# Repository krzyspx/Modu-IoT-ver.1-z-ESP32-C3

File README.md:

# Modu-IoT-ver.1-z-ESP32-C3
Projekt PCB (Eagle) dla domowej automatyki z procesorem ESP32 C3

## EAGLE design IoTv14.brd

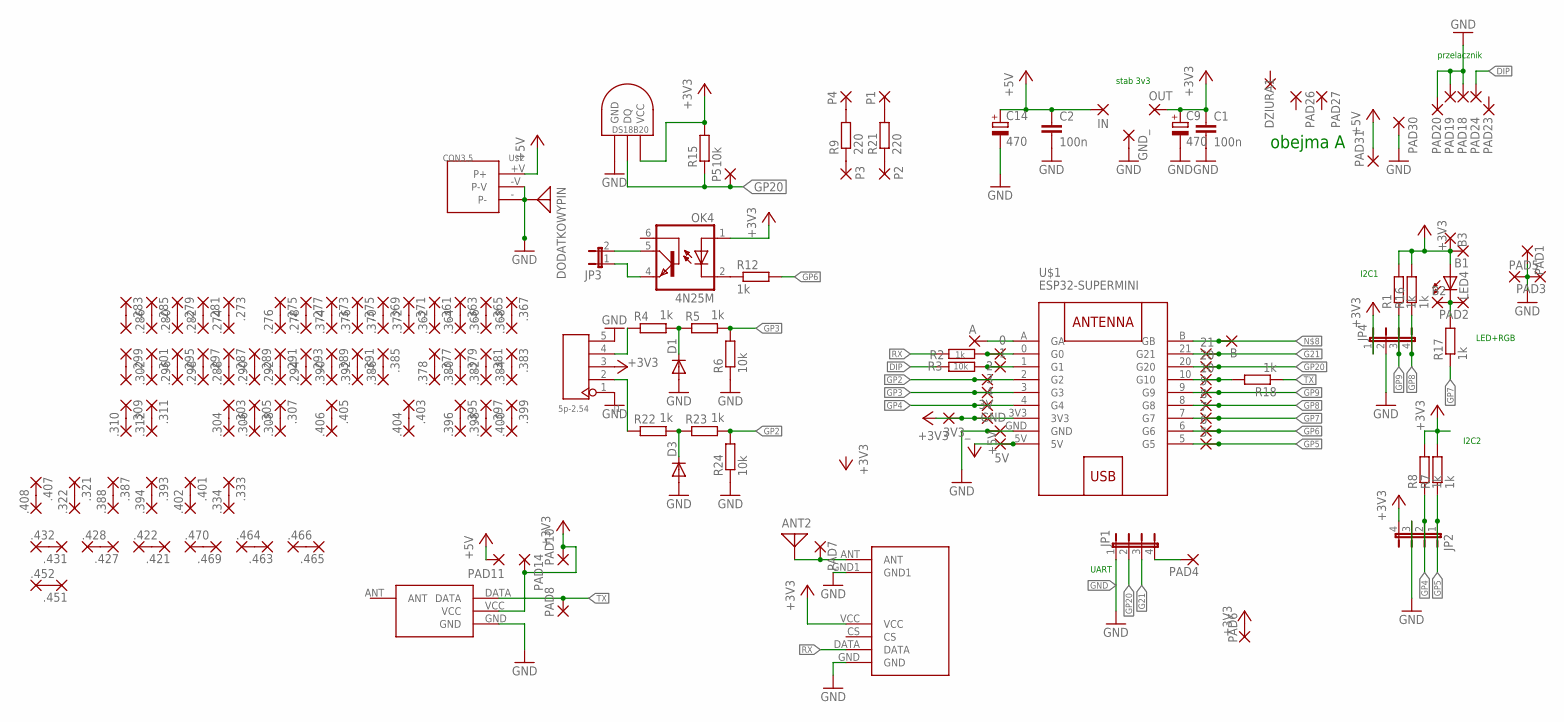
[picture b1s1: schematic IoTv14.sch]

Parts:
0, 1, 2, 3, 3V, 3V3_, 4, 5, 5V, 6, 7, 8, 9, 10, 20, 21, .273, .274, .275, .276, .277, .278, .279, .280, .281, .282, .283, .284, .285, .286, .287, .288, .289, .290, .291, .292, .293, .294, .295, .296, .297, .298, .299, .300, .301, .302, .303, .304, .305, .306, .307, .308, .309, .310, .311, .312, .321, .322, .333, .334, .361, .362, .363, .364, .365, .366, .367, .368, .369, .370, .371, .372, .373, .374, .375, .376, .377, .378, .379, .380, .381, .382, .383, .384, .385, .386, .387, .388, .389, .390, .391, .392, .393, .394, .395, .396, .397, .398, .399, .400, .401, .402, .403, .404, .405, .406, .407, .408, .421, .422, .427, .428, .431, .432, .451, .452, .463, .464, .465, .466, .469, .470: 1,6/0,8
A: 1,6/0,8
ANT2: ANTENNA; PAD-01
B, B1, B2, B3: 1,6/0,8
C1, C2: 100n; C5B2.5
C9, C14: 470; E2,5-6E
D1, D3: DIODE-DO41-7.6; DO41-7.6
DODATKOWYPIN: ANTENNA; PAD-01
DZIURA1: 3,81/1,4
GND: 1,6/0,8
GND_: 1,6/0,9
IN: 1,6/0,9
J1: 5p-2.54; H5-2.54
JP1, JP2, JP4: JP4E; JP4
JP3: JP1E; JP1
LED4: LED3MM
OK4: 4N25M; DIL06
OUT: 1,6/0,9
P1, P2, P3, P4, P5: 1,6/0,8
PAD1, PAD2, PAD3, PAD4, PAD5, PAD6, PAD7, PAD8, PAD10, PAD11, PAD14: 1,6/0,8
PAD18, PAD19, PAD24, PAD26, PAD27: 2,15/1,0
PAD20, PAD23, PAD30, PAD31: 3,81/1,4
R1, R2, R4, R5, R7, R8, R12, R16, R17, R18, R22, R23: 1k; 0204/7
R3, R6, R15, R24: 10k; 0204/7
R9, R21: 220; 0204/7
U$1: ESP32-SUPERMINI
U$2: CON3.5
U$9: DS1820TO92; DS1820
U$10: STX882
U$11: SRX822; SRX882

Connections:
+3V3: 3V.1, 3V3_.1, B1.1, B3.1, C1.1, C9.+, J1.3, JP2.4, JP4.1, LED4.A, OK4.1 (A), OUT.1, PAD6.1, PAD10.1, PAD14.1, R1.2, R7.2, R8.2, R15.2, R16.2, U$1.3V3, U$9.VDD (VCC), U$10.VCC, U$11.VCC
+5V: 5V.1, C2.1, C14.+, IN.1, PAD11.1, PAD31.1, U$1.5V, U$2.+V (P+)
DIP: PAD24.1, R3.2
G21: 21.1, JP1.3, U$1.21 (G21)
GND: C1.2, C2.2, C9.-, C14.-, D1.A, D3.A, DODATKOWYPIN.1, GND.1, GND_.1, J1.1, J1.5, JP1.1, JP2.3, JP4.2, PAD1.1, PAD3.1, PAD5.1, PAD18.1, PAD19.1, PAD20.1, PAD30.1, R6.1, R24.1, U$1.GND, U$2.-, U$2.-V, U$9.GND, U$10.GND, U$11.GND, U$11.GND1
GP2: 2.1, R23.2, R24.2, U$1.2 (G2)
GP3: 3.1, R5.2, R6.2, U$1.3 (G3)
GP4: 4.1, JP2.2, R8.1, U$1.4 (G4)
GP5: 5.1, JP2.1, R7.1, U$1.5 (G5)
GP6: 6.1, R12.2, U$1.6 (G6)
GP7: 7.1, R17.1, U$1.7 (G7)
GP8: 8.1, JP4.4, R16.1, U$1.8 (G8)
GP9: 9.1, JP4.3, R1.1, U$1.9 (G9)
GP20: 20.1, JP1.2, P5.1, R15.1, U$1.20 (G20), U$9.DQ
unnamed: 0.1, R2.2, U$1.0 (G0)
unnamed: 1.1, R3.1, U$1.1 (G1)
unnamed: 10.1, R18.2, U$1.10 (G10)
unnamed: D1.C, R4.2, R5.1
unnamed: JP3.2, OK4.5 (COL)
unnamed: J1.4, R4.1
unnamed: J1.2, R22.1
unnamed: B.1, U$1.B (GB)
unnamed: JP1.4, PAD4.1
unnamed: A.1, U$1.A (GA)
unnamed: P1.1, R21.2
unnamed: P3.1, R9.1
unnamed: P4.1, R9.2
unnamed: JP3.1, OK4.4 (EMI)
unnamed: ANT2.1, PAD7.1, U$11.ANT
unnamed: .273.1, .274.1
unnamed: .275.1, .276.1
unnamed: .277.1, .278.1
unnamed: .279.1, .280.1
unnamed: .281.1, .282.1
unnamed: .283.1, .284.1
unnamed: .285.1, .286.1
unnamed: .287.1, .288.1
unnamed: .289.1, .290.1
unnamed: .291.1, .292.1
unnamed: .293.1, .294.1
unnamed: .295.1, .296.1
unnamed: .297.1, .298.1
unnamed: .299.1, .300.1
unnamed: .301.1, .302.1
unnamed: .303.1, .304.1
unnamed: .305.1, .306.1
unnamed: .307.1, .308.1
unnamed: .309.1, .310.1
unnamed: .311.1, .312.1
unnamed: .321.1, .322.1
unnamed: .333.1, .334.1
unnamed: .361.1, .362.1
unnamed: .363.1, .364.1
unnamed: .365.1, .366.1
unnamed: .367.1, .368.1
unnamed: .369.1, .370.1
unnamed: .371.1, .372.1
unnamed: .373.1, .374.1
unnamed: .375.1, .376.1
unnamed: .377.1, .378.1
unnamed: .379.1, .380.1
unnamed: .381.1, .382.1
unnamed: .383.1, .384.1
unnamed: .385.1, .386.1
unnamed: .387.1, .388.1
unnamed: .389.1, .390.1
unnamed: .391.1, .392.1
unnamed: .393.1, .394.1
unnamed: .395.1, .396.1
unnamed: .397.1, .398.1
unnamed: .399.1, .400.1
unnamed: .401.1, .402.1
unnamed: .403.1, .404.1
unnamed: .405.1, .406.1
unnamed: .407.1, .408.1
unnamed: .421.1, .422.1
unnamed: .427.1, .428.1
unnamed: .431.1, .432.1
unnamed: .451.1, .452.1
unnamed: .463.1, .464.1
unnamed: .465.1, .466.1
unnamed: .469.1, .470.1
unnamed: B2.1, LED4.K (C), PAD2.1, R17.2
unnamed: P2.1, R21.1
unnamed: D3.C, R22.2, R23.1
unnamed: OK4.2 (C), R12.1
RX: R2.1, U$11.DATA
TX: PAD8.1, R18.1, U$10.DATA

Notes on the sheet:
przelacznik
stab 3v3
obejma A
UART
I2C1
I2C2
LED+RGB

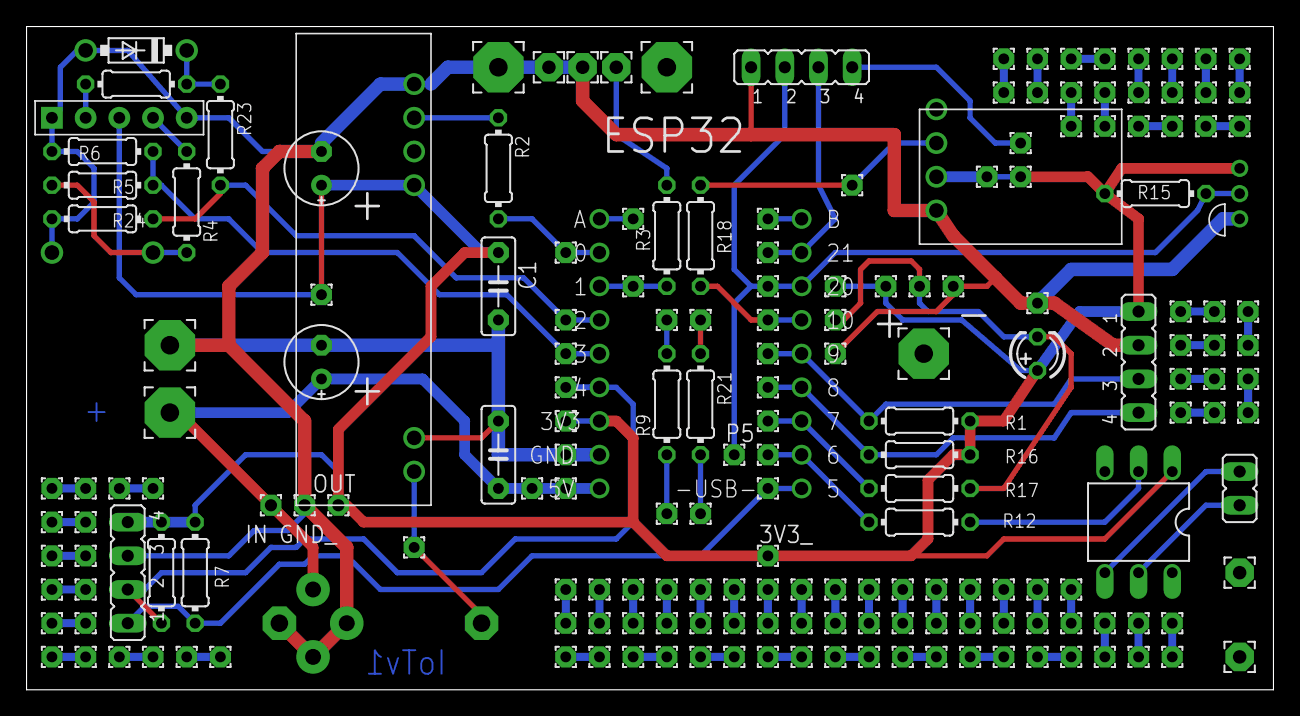
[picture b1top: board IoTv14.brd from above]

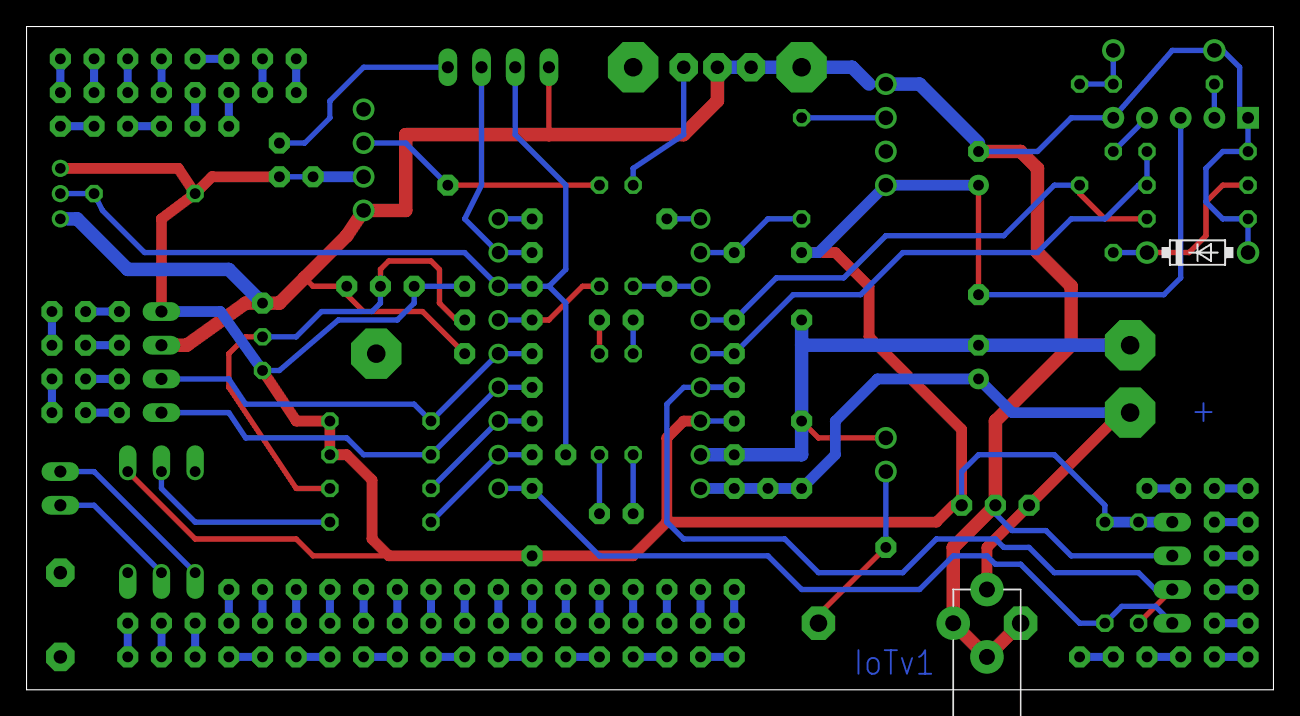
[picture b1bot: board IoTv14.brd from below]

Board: 2 copper layers, 94.0 x 50.0 mm, 195 parts (2 on the bottom side), 88 nets.
